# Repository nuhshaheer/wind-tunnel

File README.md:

# Wind Tunnel

> **Status (2026-11-26): pre-build, sized; CAD in progress.** Every part except the fan has arrived (2026-11-17). The tunnel
> is not built, but it is fully sized (build step 1, 2026-11-26): every printed part has a dimension sheet, with points
> files for Fusion 360, in [cad/sizing/](cad/sizing/README.md), and the
> [drawing package](docs/drawings/README.md) is at revision F. The sensor circuit is drawn (drawing package sheets 11–12), explained in
> [docs/electronics_walkthrough.md](docs/electronics_walkthrough.md), and built on a breadboard, where every sensor
> reads with its bring-up sketch in [firmware/](firmware/README.md) (2026-11-23). The shield PCB that will replace the
> breadboard is designed in KiCad ([PCB/arduino_shield/](PCB/arduino_shield/)) and **ordered (2026-11-26)**. Data so far:
> the calibration weights' true masses (EXP-001, 2026-11-19) and the load cell on a printed bench scale (EXP-002,
> 2026-11-26: 13,727.5 counts/g, straight within 0.025 g; its zero is the limit; Preliminary). The settling chamber,
> diffuser, fan inlet ring and contraction are drawn as CAD and checked (`cad/main cad files/`, measured with
> `scripts/check_mesh.py`). Next: the corner-piece cuts, the test section, the test coupons, and a combined logging
> sketch.
> The authoritative current state is [PROJECT_STATUS.md](PROJECT_STATUS.md); the next tasks are in [TODO.md](TODO.md).
> The complete parts list is [docs/buy_list.md](docs/buy_list.md), and the order tracker is
> [docs/shopping_list.md](docs/shopping_list.md).

## Goal
Measure drag, and prove the tunnel reads true.

## What this project is about
A small wind tunnel with my own instrumentation: flow conditioning, a pitot tube for airspeed, and a load cell for drag force, read through an interface board I design with parts from my ECE kit. Before trusting any other result, I validate the tunnel by measuring something with a known answer: the drag coefficient of a sphere (about 0.42–0.445 at this tunnel's Reynolds number, ±10 %; the original plan said ~0.47). It's the same move as the 100 MΩ resistor on the STM.

## Why it matters
Of the three projects, this is the only one that shows me as a mechanical engineer doing fluids, which is the work aerospace companies hire MEs into.

## Hardware (as of 2026-11-26)

The tunnel: an open-circuit blower with the fan at the front, a 100 mm × 100 mm test section, 3D-printed in bolted
segments, with a 13 m/s target top speed ([DECISIONS.md](DECISIONS.md) D-005, D-007, D-008, D-010, D-013).
Sized on 2026-11-26 (D-022 to D-030): a 175 mm three-screen diffuser, a 275 mm settling chamber with a printed
honeycomb, a 250 mm 5th-order contraction (ratio 6.25) and a 310 mm test section, about 1.40 m in all with the fan;
the 250 mm sections print as four corner pieces glued together.
The model sits on a brass sting that rises through a replaceable floor insert, with the sting shield attached to the
insert; the top window lifts off on magnets, and the sting clamps into a printed mount on the load cell (D-014 to
D-016). Reasons, prices and alternatives for every part: [docs/buy_list.md](docs/buy_list.md).

### On hand
- Bambu Lab P1S 3D printer, PLA, PETG-CF and a hardened-steel nozzle
- Elegoo Mega 2560 (working: Blink upload verified 2026-11-02)
- ECE2010 lab kit (op-amps, regulators, breadboard, jumpers)
- Soldering station, bench power supply, calipers, hand drill, spirit level, 43 magnets (8 × 2 mm), access to a school
  lab balance, and a borrowed multimeter (my own is on order)

### Arrived 2026-11-17 (ordered 2026-11-09/10; most checks still to do)
- Airspeed: a Sensirion SDP810-125Pa differential pressure sensor, with a home-made brass pitot probe and wall
  pressure taps
- Drag: two TAL221 100 g load cells and a SparkFun HX711
- Air density: a Waveshare BME280 (pressure, temperature, humidity)
- Flow conditioning: aluminium window screen (the honeycomb is printed)
- Validation models: 3/4 in and 1 in Delrin balls, each on its own brass sting
- Build parts: black PLA, 1/8 in cast acrylic windows, heat-set inserts, screws, tubing and fittings, neoprene, tools
  and a calibration weight set

### Still to buy
- The fan: AC Infinity CLOUDLINE S6 (D-025), bought last, once the airspeed readout works

### Changed from the original plan
- No servo for the airfoil pitch: preset angles instead (2026-11-01)
- No ducting: the fan's collar slides into a printed inlet
- No bought pitot tube: made in-house from brass tube
- No on-tunnel display or knob: all output goes to the laptop (D-012)
- No op-amp signal conditioning: the sensors are digital, so the circuit is an interface board (connectors, two
  capacitors, optional pull-ups) on the laptop's USB power, breadboard first, then a PCB shield on the Mega
  (D-018, Accepted 2026-11-26; shield ordered)

## Build order
1. Size the contraction and test section: done for the whole tunnel (2026-11-26); the CAD is in progress ← **now**
2. Flow conditioning (honeycomb + screens)
3. Map flow uniformity across the test section with the pitot tube
4. Load cell and its conditioning circuit
5. Calibrate against known weights
6. Validation run (sphere Cd)
7. Airfoil tests at preset angles

## Result / deliverable
The measured Cd of a sphere compared against the published value at the same Reynolds number: Brown and Lawler (2003)
Eq. (19), about 0.42–0.445 for the planned runs, ±10 %, plus a check that Cd rises with Re as predicted
([DECISIONS.md](DECISIONS.md) D-009). The original plan compared against ~0.47.

---

## Repository structure

```text
CLAUDE.md                 Instructions for AI agents (rules, reading order, conventions)
PROJECT_STATUS.md         Authoritative snapshot of the current state
PROJECT_BACKGROUND.md     Goals, physics and equations, uncertainty sources, references
DECISIONS.md              Chronological technical decisions
TODO.md                   Prioritized tasks with verification criteria
docs/
  experimental_setup.md   The physical setup as built (Unknown until decided)
  buy_list.md             Everything to buy, what each part does, prices, and what is on hand
  shopping_list.md        The owner's order tracker: item, qty, price, link, status (To buy → Ordered → Got it)
  data_catalog.md         Every dataset/experiment and how it was processed
  electronics_walkthrough.md  The sensor circuit explained step by step for a beginner, with bring-up steps
  forms/                  Fill-in forms for lab and bench work (calibration-mass weighing sheet)
  images/                 Pictures used by the docs (drawing snapshots, bench photos)
  sessions/               One log per work session + SESSION_LOG.md index
  sketches/               The owner's hand sketches of the tunnel (intent, not as built)
  drawings/               Preliminary drawing package (HTML: 10 mechanical + 2 electrical sheets) and its generator
data/README.md            Data layout and rules (raw vs processed, naming, units, large files)
firmware/                 Arduino sketches for the Mega 2560 (one folder per sketch); index in firmware/README.md
PCB/arduino_shield/       The owner's KiCad 10 project for the sensor shield (D-020); gerbers/ holds the manufacturing files
cad/                      CAD: sizing/ holds the dimension sheets, "main cad files/" the owner's Fusion exports (3MF);
                          third-party/ holds downloaded designs with their licence (a TAL221 bench scale)
resources/                Reference papers (PDFs) with reading notes; index and naming rules in resources/README.md
scripts/                  Helper scripts used by /catchup and /wrap, and serial_capture.ps1 (records the Mega's output to CSV)
data/raw/, data/processed/  Datasets (raw files never edited; processed files regenerated by scripts); see data/README.md
analysis/                 Analysis scripts (raw data -> data/processed/ and results/)
results/                  Result summaries cited by the docs
tests/                    Tests for the helper scripts
.claude/                  Agent commands (skills/) and the no-push permission rule (settings.json)
```

## Documentation

Start with [PROJECT_STATUS.md](PROJECT_STATUS.md) and [TODO.md](TODO.md). Then
[PROJECT_BACKGROUND.md](PROJECT_BACKGROUND.md), [DECISIONS.md](DECISIONS.md),
[docs/experimental_setup.md](docs/experimental_setup.md), [docs/data_catalog.md](docs/data_catalog.md) and the
[session log index](docs/sessions/SESSION_LOG.md).

## Data and analysis workflow

- Raw sensor logs go in `data/raw/YYYY-MM-DD_EXP-NNN_description/` and are never edited.
- Scripts in `analysis/` turn raw data into `data/processed/` and `results/`; every result is reproducible from raw data + script.
- Every dataset gets an entry in [docs/data_catalog.md](docs/data_catalog.md).
- Videos stay out of Git (external storage, referenced from the catalog); Git LFS is not enabled yet ([DECISIONS.md](DECISIONS.md) D-004).

To record data from the Mega (Arduino IDE closed; stop with Ctrl+C), and to rerun the one analysis so far:

```bash
powershell -NoProfile -ExecutionPolicy Bypass -File scripts\serial_capture.ps1 -Port COM3 -OutFile data\raw\<folder>\run01.csv
python analysis/exp002_bench_scale.py      # EXP-002: load cell on the bench scale -> data/processed/, results/
```

## Requirements and checks

The helper scripts need only Python 3 (standard library; Python 3.9 or newer expected) and Git. The tests pass on
Python 3.11 on Windows 11 (last run 2026-11-26); earlier sessions used 3.13. `scripts/serial_capture.ps1` needs only
Windows PowerShell 5.1 ([DECISIONS.md](DECISIONS.md) D-021).

```bash
python -m unittest discover -s tests -v   # tests for the helper scripts
python scripts/check_docs.py              # documentation consistency, file-size and secret checks
python scripts/sync_status.py --fetch     # where the local branch stands relative to GitHub
```

## Working with AI agents: `/catchup` and `/wrap`

These are Claude Code project skills in `.claude/skills/`. Type them in a Claude Code session opened in this folder.
They are plain Markdown, so other agents can follow them by reading the files.

- **`/catchup`** (start of a session): fetches from GitHub and fast-forwards only when that cannot touch local work;
  reads the docs in order; checks them against the actual files; reports the state, discrepancies and the first task.
  Add a request after it, e.g. `/catchup size the test section`.
- **`/wrap`** (end of a session): audits the whole project, updates every document that needs it, writes or updates
  the session log, runs the tests and checks, and prints the exact Git commands for you to run.
  `/wrap commit` also lets the agent make one local commit. **Agents never push.** `.claude/settings.json` denies
  `git push` for agents, and `CLAUDE.md` forbids it.

## Pushing to GitHub (manual)

GitHub repository: https://github.com/nuhshaheer/wind-tunnel (public since 2026-11-26, D-031; the account was `nuhshaheer-2007` until
2026-11-02, and the old URL redirects). Remote `origin`, branch `main`.
Run in PowerShell or Git Bash (the VS Code terminal is fine):

```bash
cd "C:/Users/nuhbm/OneDrive/Desktop/nuhs projects/2 - Wind Tunnel"
git status                       # what changed
git diff                         # review changes to tracked files
git add <files listed by /wrap>  # stage specific files, never blindly everything
git diff --cached                # review exactly what will be committed
git commit -m "Summary" -m "Why"
git push                         # first time: git push -u origin main
```

If GitHub has commits you don't have, run `git pull --rebase origin main` before pushing. `/wrap` tells you when that
applies and what to do about conflicts.

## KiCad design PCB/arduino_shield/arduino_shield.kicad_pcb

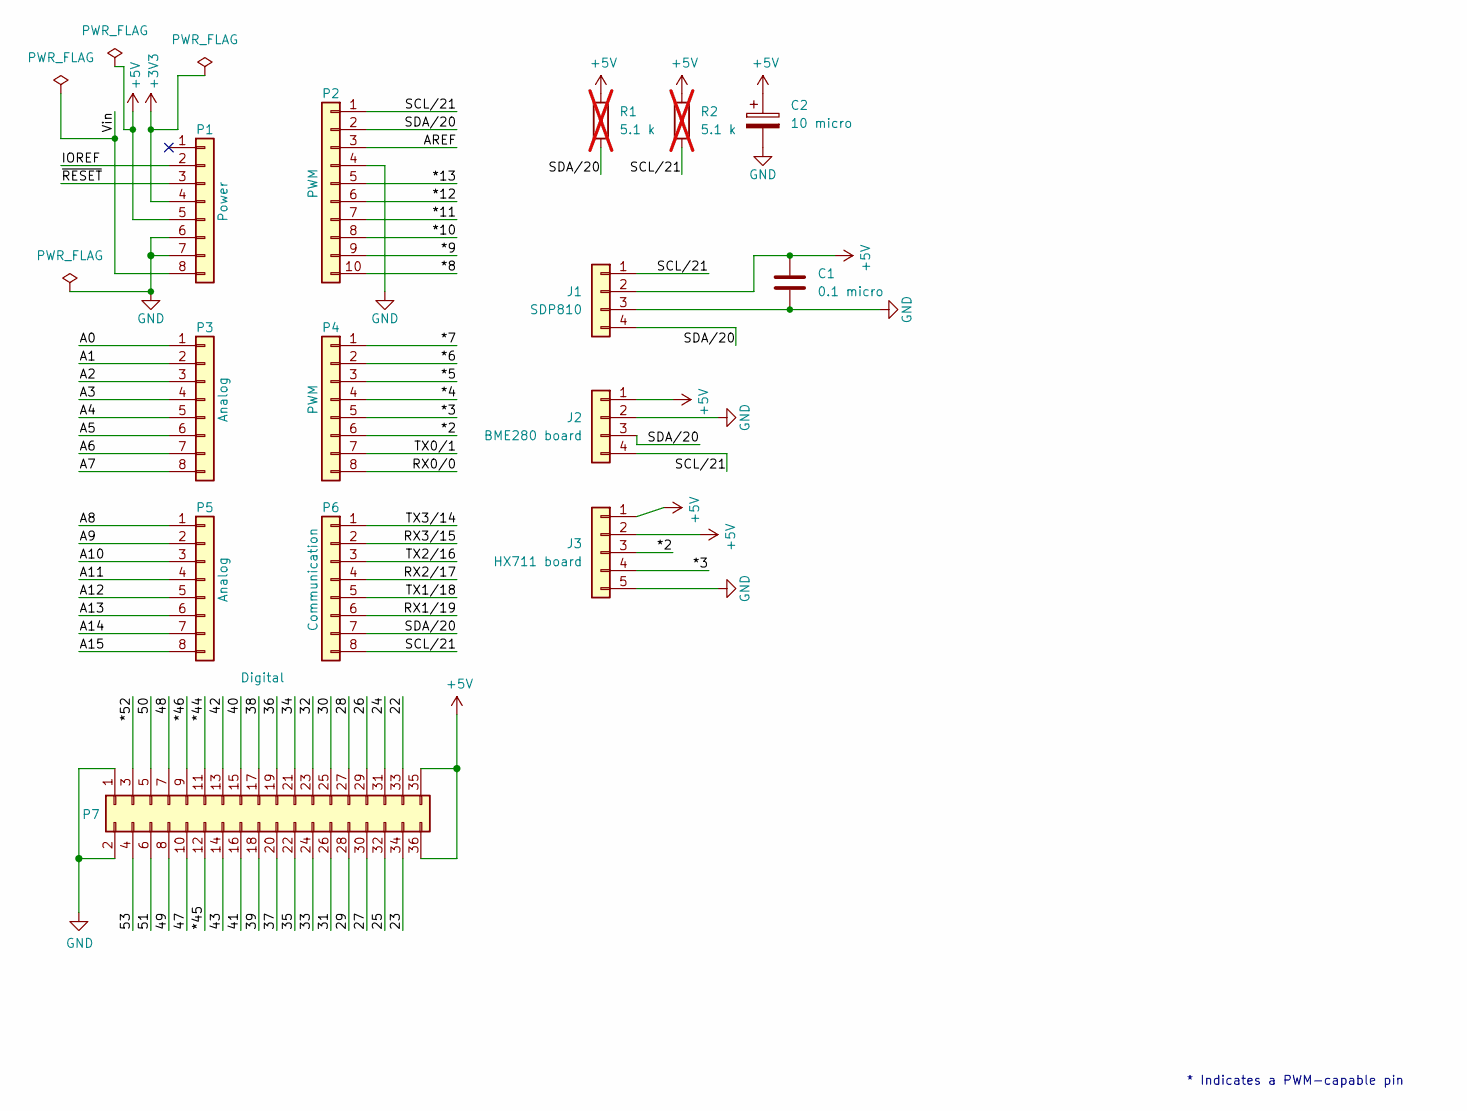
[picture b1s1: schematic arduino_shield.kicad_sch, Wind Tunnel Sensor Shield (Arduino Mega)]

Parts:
C1: 0.1 micro; C_Disc_D5.0mm_W2.5mm_P5.00mm
C2: 10 micro; CP_Radial_D5.0mm_P2.00mm
J1: SDP810; PinHeader_1x04_P2.54mm_Vertical
J2: BME280 board; PinHeader_1x04_P2.54mm_Vertical
J3: HX711 board; PinHeader_1x05_P2.54mm_Vertical
P1: Power; PinSocket_1x08_P2.54mm_Vertical
P2: PWM; PinSocket_1x10_P2.54mm_Vertical
P3, P5: Analog; PinSocket_1x08_P2.54mm_Vertical
P4: PWM; PinSocket_1x08_P2.54mm_Vertical
P6: Communication; PinSocket_1x08_P2.54mm_Vertical
P7: Digital; PinSocket_2x18_P2.54mm_Vertical
R1, R2: 5.1 k; R_Axial_DIN0207_L6.3mm_D2.5mm_P10.16mm_Horizontal; not fitted

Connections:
+3V3: P1.4
+5V: C1.1, C2.1, J1.2, J2.1, J3.1, J3.2, P1.5, P7.35, P7.36, R1.1, R2.1
/22: P7.33
/23: P7.34
/24: P7.31
/25: P7.32
/26: P7.29
/27: P7.30
/28: P7.27
/29: P7.28
/30: P7.25
/31: P7.26
/32: P7.23
/33: P7.24
/34: P7.21
/35: P7.22
/36: P7.19
/37: P7.20
/38: P7.17
/39: P7.18
/40: P7.15
/41: P7.16
/42: P7.13
/43: P7.14
/47: P7.10
/48: P7.7
/49: P7.8
/50: P7.5
/51: P7.6
/53: P7.4
/*2: J3.3, P4.6
/*3: J3.4, P4.5
/*4: P4.4
/*5: P4.3
/*6: P4.2
/*7: P4.1
/*8: P2.10
/*9: P2.9
/*10: P2.8
/*11: P2.7
/*12: P2.6
/*13: P2.5
/*44: P7.11
/*45: P7.12
/*46: P7.9
/*52: P7.3
/A0: P3.1
/A1: P3.2
/A2: P3.3
/A3: P3.4
/A4: P3.5
/A5: P3.6
/A6: P3.7
/A7: P3.8
/A8: P5.1
/A9: P5.2
/A10: P5.3
/A11: P5.4
/A12: P5.5
/A13: P5.6
/A14: P5.7
/A15: P5.8
/AREF: P2.3
/IOREF: P1.2
/RX0/0: P4.8
/RX1/19: P6.6
/RX2/17: P6.4
/RX3/15: P6.2
/SCL/21: J1.1, J2.4, P2.1, P6.8, R2.2
/SDA/20: J1.4, J2.3, P2.2, P6.7, R1.2
/TX0/1: P4.7
/TX1/18: P6.5
/TX2/16: P6.3
/TX3/14: P6.1
/Vin: P1.8
/~RESET: P1.3
GND: C1.2, C2.2, J1.3, J2.2, J3.5, P1.6, P1.7, P2.4, P7.1, P7.2

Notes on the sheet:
* Indicates a PWM-capable pin

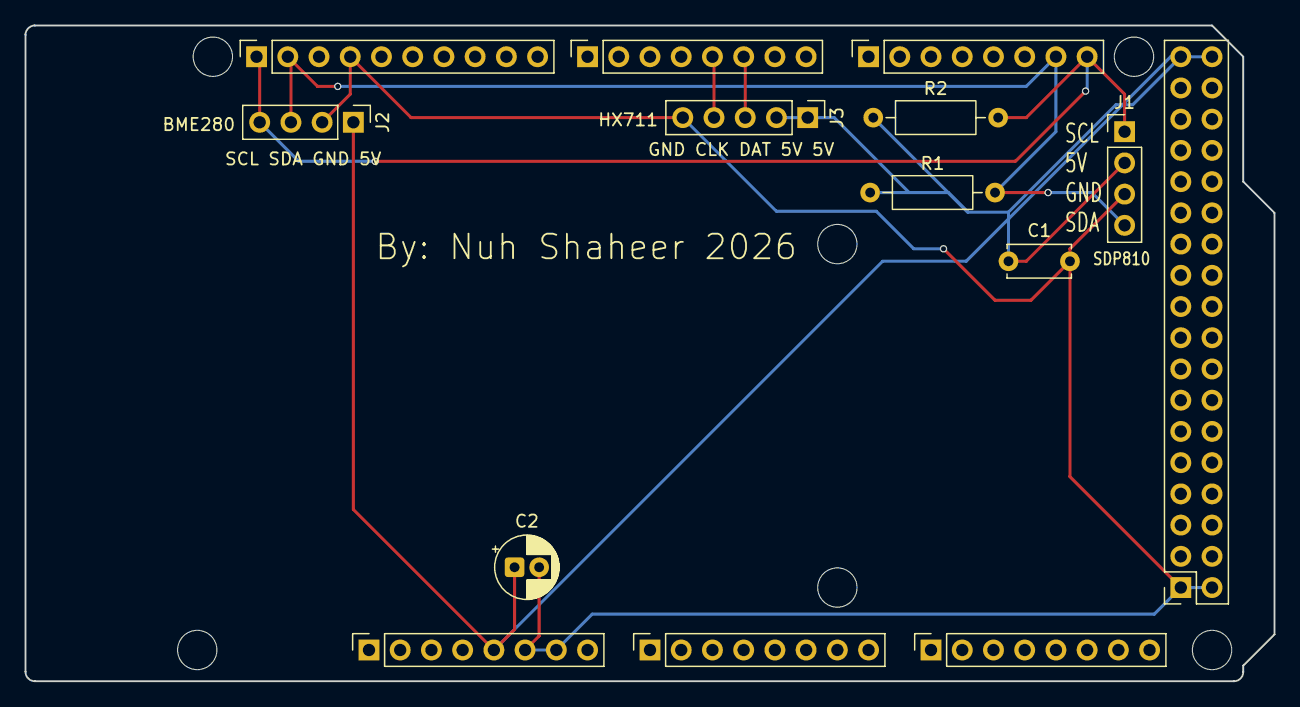
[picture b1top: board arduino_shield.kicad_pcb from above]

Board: 2 copper layers, 101.6 x 53.3 mm, 20 parts (0 on the bottom side), 6 nets.

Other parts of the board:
MH1, MH2, MH3, MH4, MH5, MH6: MountingHole_3.2mm
